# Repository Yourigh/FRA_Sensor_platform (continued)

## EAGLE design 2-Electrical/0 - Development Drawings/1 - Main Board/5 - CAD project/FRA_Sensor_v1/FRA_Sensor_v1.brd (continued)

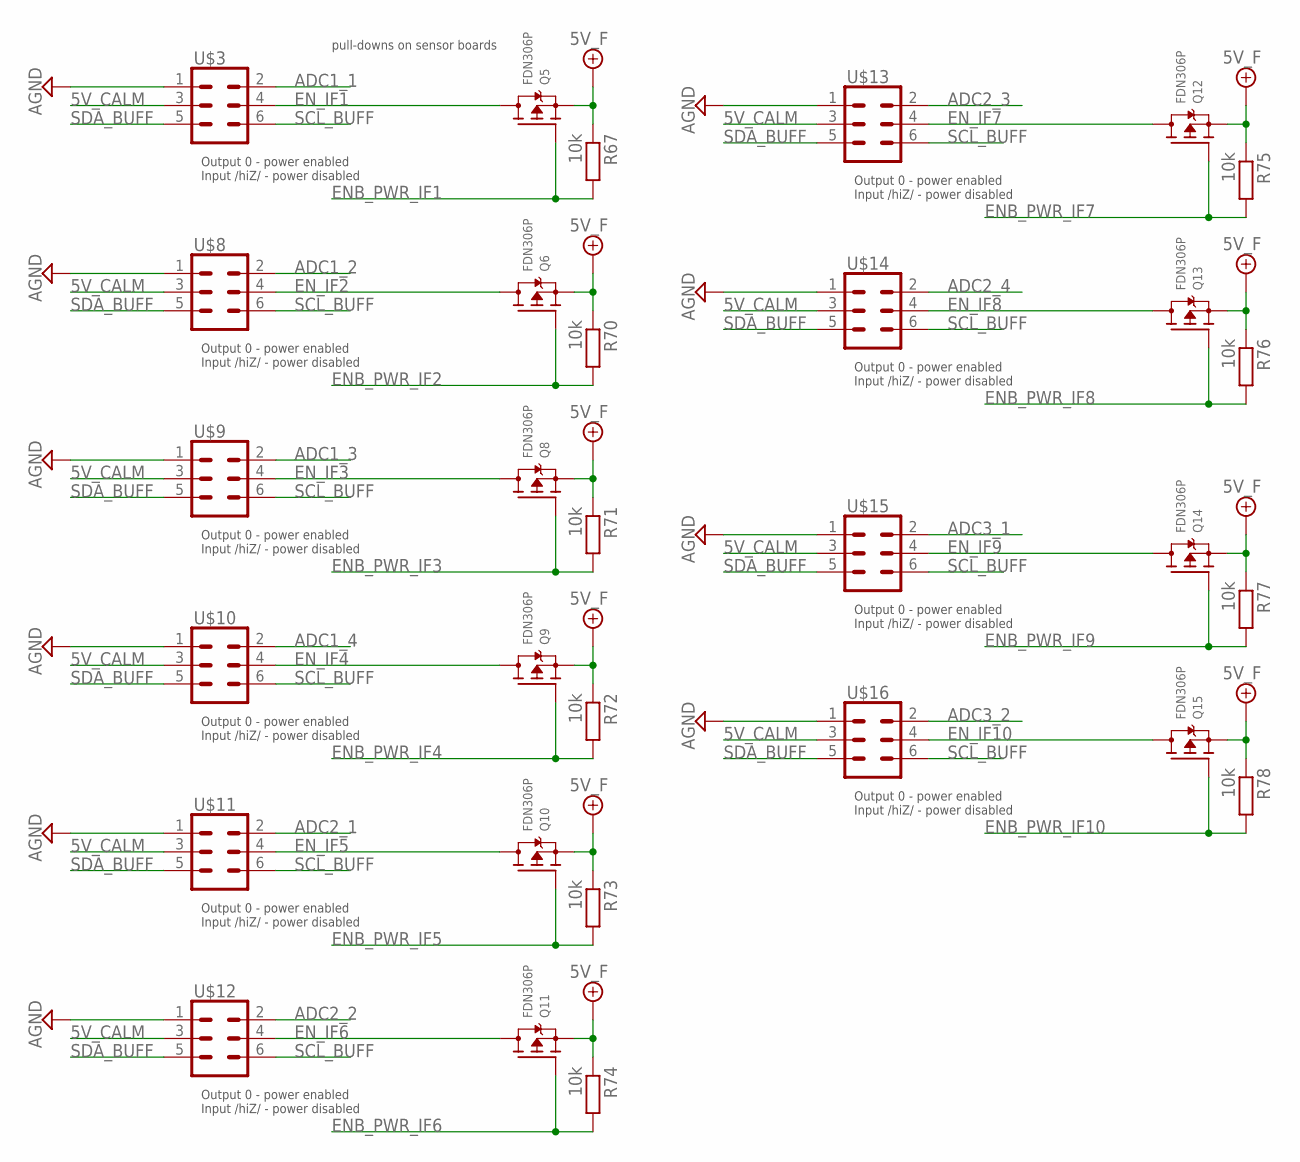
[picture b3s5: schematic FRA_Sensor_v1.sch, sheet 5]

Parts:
Q5, Q6, Q8, Q9, Q10, Q11, Q12, Q13, Q14, Q15: FDN306P; SOT23-WIDE; PARTNO FDN306P
R67, R70, R71, R72, R73, R74, R75, R76, R77, R78: 10k; R0603; PARTNO CRCW060310K0JNEAC
U$3, U$8, U$9, U$10, U$11, U$12, U$13, U$14, U$15, U$16: CONN_03X2_WE_61200621621; WE_61200621621; PARTNO 61200621621

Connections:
5V_CALM: U$3.3, U$8.3, U$9.3, U$10.3, U$11.3, U$12.3, U$13.3, U$14.3, U$15.3, U$16.3; also elsewhere on the board
+5V/1: Q5.2 (S), Q6.2 (S), Q8.2 (S), Q9.2 (S), Q10.2 (S), Q11.2 (S), Q12.2 (S), Q13.2 (S), Q14.2 (S), Q15.2 (S), R67.1, R70.1, R71.1, R72.1, R73.1, R74.1, R75.1, R76.1, R77.1, R78.1; also elsewhere on the board
ADC1_1: U$3.2; also elsewhere on the board
ADC1_2: U$8.2; also elsewhere on the board
ADC1_3: U$9.2; also elsewhere on the board
ADC1_4: U$10.2; also elsewhere on the board
ADC2_1: U$11.2; also elsewhere on the board
ADC2_2: U$12.2; also elsewhere on the board
ADC2_3: U$13.2; also elsewhere on the board
ADC2_4: U$14.2; also elsewhere on the board
ADC3_1: U$15.2; also elsewhere on the board
ADC3_2: U$16.2; also elsewhere on the board
AGND: U$3.1, U$8.1, U$9.1, U$10.1, U$11.1, U$12.1, U$13.1, U$14.1, U$15.1, U$16.1; also elsewhere on the board
ENB_PWR_IF1: Q5.1 (G), R67.2; also elsewhere on the board
ENB_PWR_IF2: Q6.1 (G), R70.2; also elsewhere on the board
ENB_PWR_IF3: Q8.1 (G), R71.2; also elsewhere on the board
ENB_PWR_IF4: Q9.1 (G), R72.2; also elsewhere on the board
ENB_PWR_IF5: Q10.1 (G), R73.2; also elsewhere on the board
ENB_PWR_IF6: Q11.1 (G), R74.2; also elsewhere on the board
ENB_PWR_IF7: Q12.1 (G), R75.2; also elsewhere on the board
ENB_PWR_IF8: Q13.1 (G), R76.2; also elsewhere on the board
ENB_PWR_IF9: Q14.1 (G), R77.2; also elsewhere on the board
ENB_PWR_IF10: Q15.1 (G), R78.2; also elsewhere on the board
EN_IF1: Q5.3 (D), U$3.4
EN_IF2: Q6.3 (D), U$8.4
EN_IF3: Q8.3 (D), U$9.4
EN_IF4: Q9.3 (D), U$10.4
EN_IF5: Q10.3 (D), U$11.4
EN_IF6: Q11.3 (D), U$12.4
EN_IF7: Q12.3 (D), U$13.4
EN_IF8: Q13.3 (D), U$14.4
EN_IF9: Q14.3 (D), U$15.4
EN_IF10: Q15.3 (D), U$16.4
SCL_BUFF: U$3.6, U$8.6, U$9.6, U$10.6, U$11.6, U$12.6, U$13.6, U$14.6, U$15.6, U$16.6; also elsewhere on the board
SDA_BUFF: U$3.5, U$8.5, U$9.5, U$10.5, U$11.5, U$12.5, U$13.5, U$14.5, U$15.5, U$16.5; also elsewhere on the board

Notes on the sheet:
Output 0 - power enabled Input /hiZ/ - power disabled
pull-downs on sensor boards

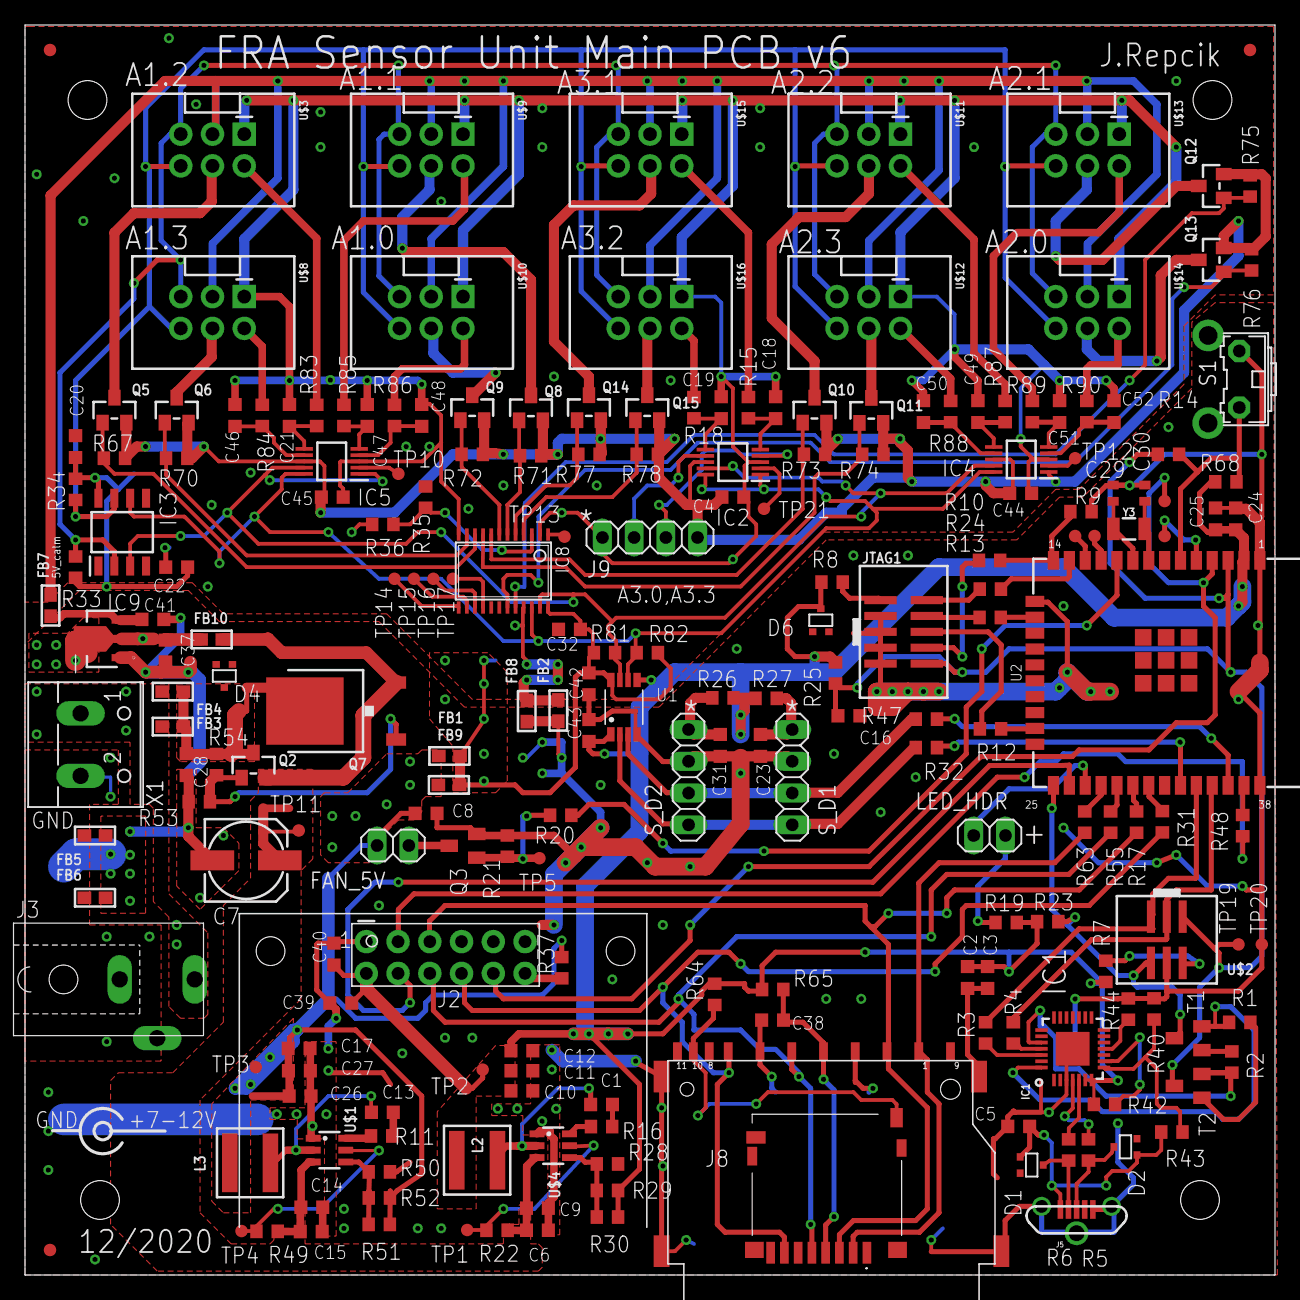
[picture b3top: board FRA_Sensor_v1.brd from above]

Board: 2 copper layers, 100.0 x 100.0 mm, 214 parts (1 on the bottom side), 138 nets.

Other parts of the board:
DRILEGEND: DRILEGEND

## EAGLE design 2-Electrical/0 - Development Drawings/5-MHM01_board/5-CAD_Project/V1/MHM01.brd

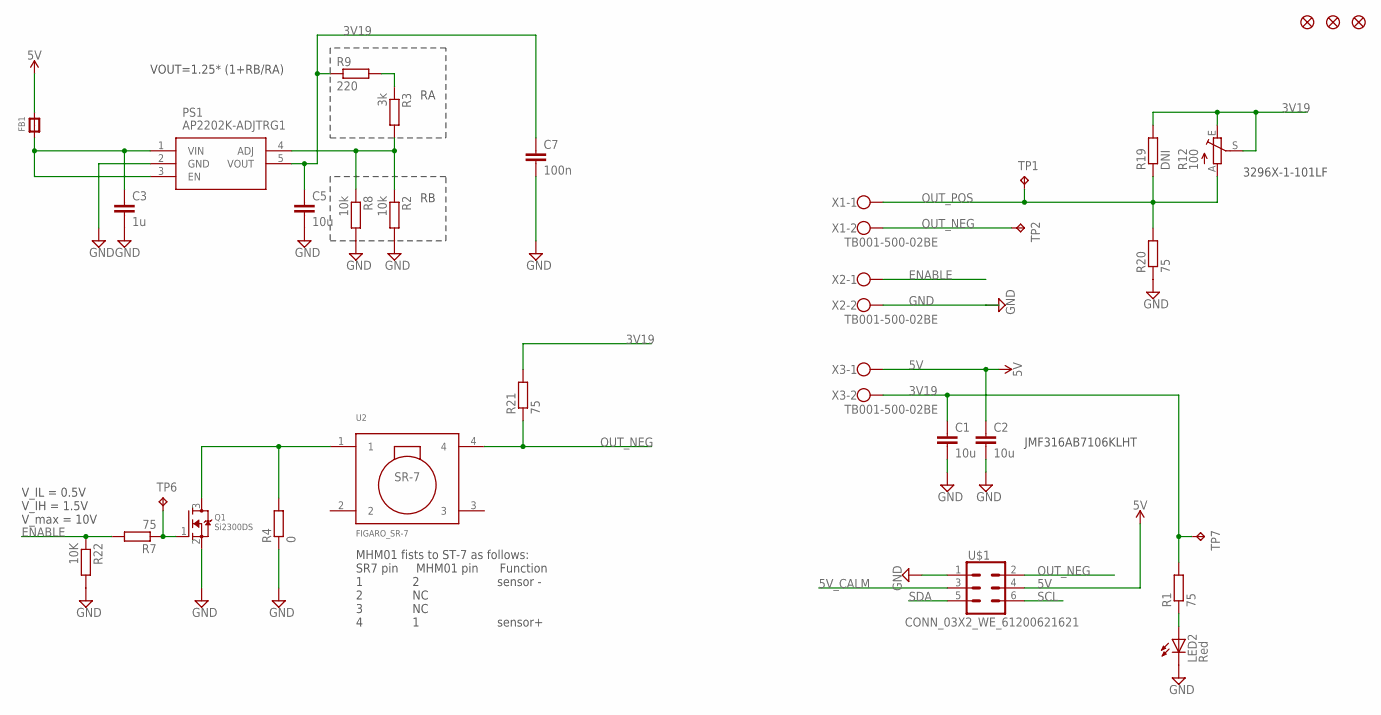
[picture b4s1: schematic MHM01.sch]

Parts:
C1, C2: 10u; C1206; PARTNO JMF316AB7106KLHT
C3: 1u; C0603K; PARTNO GRM188R71C105KE15D
C5: 10u; C0603K; PARTNO GRM188R61A106KE69J
C7: 100n; C0603K; PARTNO CC0603KRX7R8BB104
FB1: FERRITE; 0603; PARTNO BLM18PG121SN1D
FID1, FID2, FID4: FIDUCIAL""; FIDUCIAL_1MM
LED2: Red; CHIPLED_1206; PARTNO BR1101W-TR
PS1: AP2202K-ADJTRG1; SOT95P280X145-5N; PARTNO AP2202K-ADJTRG1
Q1: Si2300DS; SOT23; PARTNO JMF316AB7106KLHT
R1, R7, R20, R21: 75; R1206; PARTNO CRCW120675R0FKEA
R2, R8: 10k; R0603; PARTNO CRCW060310K0FKEA
R3: 3k; R0603; PARTNO ERA-3AEB302V
R4: 0; R1206; PARTNO CRCW12060000Z0EA
R9: 220; R0603; PARTNO CRCW0603220RFKEA
R12: 100; RJ9W; PARTNO 3296X-1-101LF
R19: DNI; R1206
R22: 10K; R1206; PARTNO CRCW120610K0FKEA
TP1, TP2, TP6, TP7: TPTP10R; TP10R
U2: FIGARO_SR-7; FIGARO-SR7; PARTNO SR-7
U$1: CONN_03X2_WE_61200621621; WE_61200621621; PARTNO 61200621621
X1, X2, X3: TB001-500-02BE; W237-102; PARTNO TB001-500-02BE

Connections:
3V19: C1.1, C5.1, C7.1, PS1.5 (VOUT), R1.2, R9.1, R12.E, R12.S, R19.2, R21.2, TP7.TP, X3.2
5V: C2.1, FB1.2, U$1.4, X3.1
5V_CALM: U$1.3
ENABLE: R7.2, R22.1, X2.1
GND: C1.2, C2.2, C3.2, C5.2, C7.2, LED2.C, PS1.2 (GND), Q1.2 (S), R2.2, R4.1, R8.2, R20.1, R22.2, U$1.1, X2.2
unnamed: LED2.A, R1.1
unnamed: PS1.4 (ADJ), R2.1, R3.2, R8.1
unnamed: C3.1, FB1.1, PS1.1 (VIN), PS1.3 (EN)
unnamed: Q1.3 (D), R4.2, U2.1
unnamed: R3.1, R9.2
unnamed: Q1.1 (G), R7.1, TP6.TP
OUT_NEG: R21.1, TP2.TP, U2.4, U$1.2, X1.2
OUT_POS: R12.A, R19.1, R20.2, TP1.TP, X1.1
SCL: U$1.6
SDA: U$1.5

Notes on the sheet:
MHM01 fists to ST-7 as follows: SR7 pin MHM01 pin Function 1 2 sensor - 2 NC 3 NC 4 1 sensor+
VOUT=1.25* (1+RB/RA)
JMF316AB7106KLHT
3296X-1-101LF
V_IL = 0.5V V_IH = 1.5V V_max = 10V

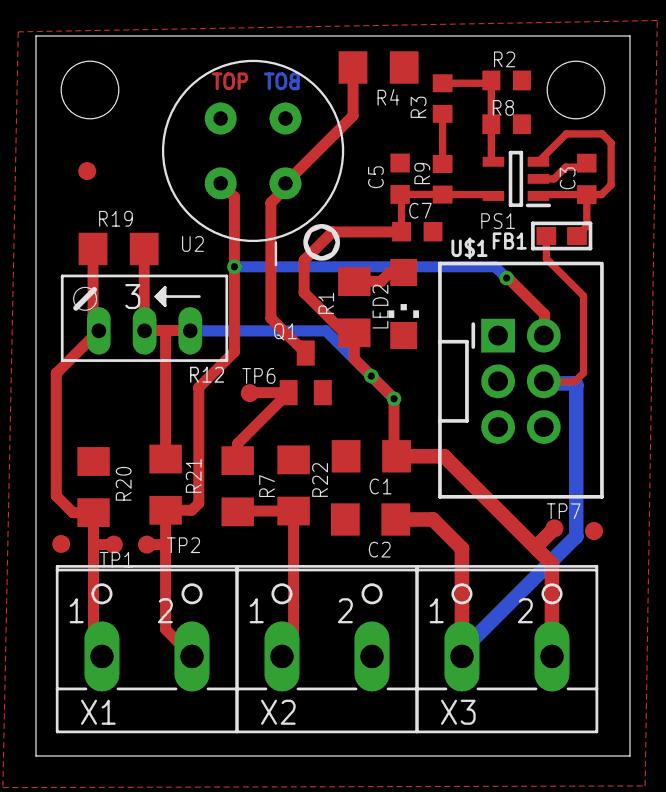
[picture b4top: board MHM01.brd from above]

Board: 2 copper layers, 33.0 x 40.0 mm, 33 parts (0 on the bottom side), 12 nets.

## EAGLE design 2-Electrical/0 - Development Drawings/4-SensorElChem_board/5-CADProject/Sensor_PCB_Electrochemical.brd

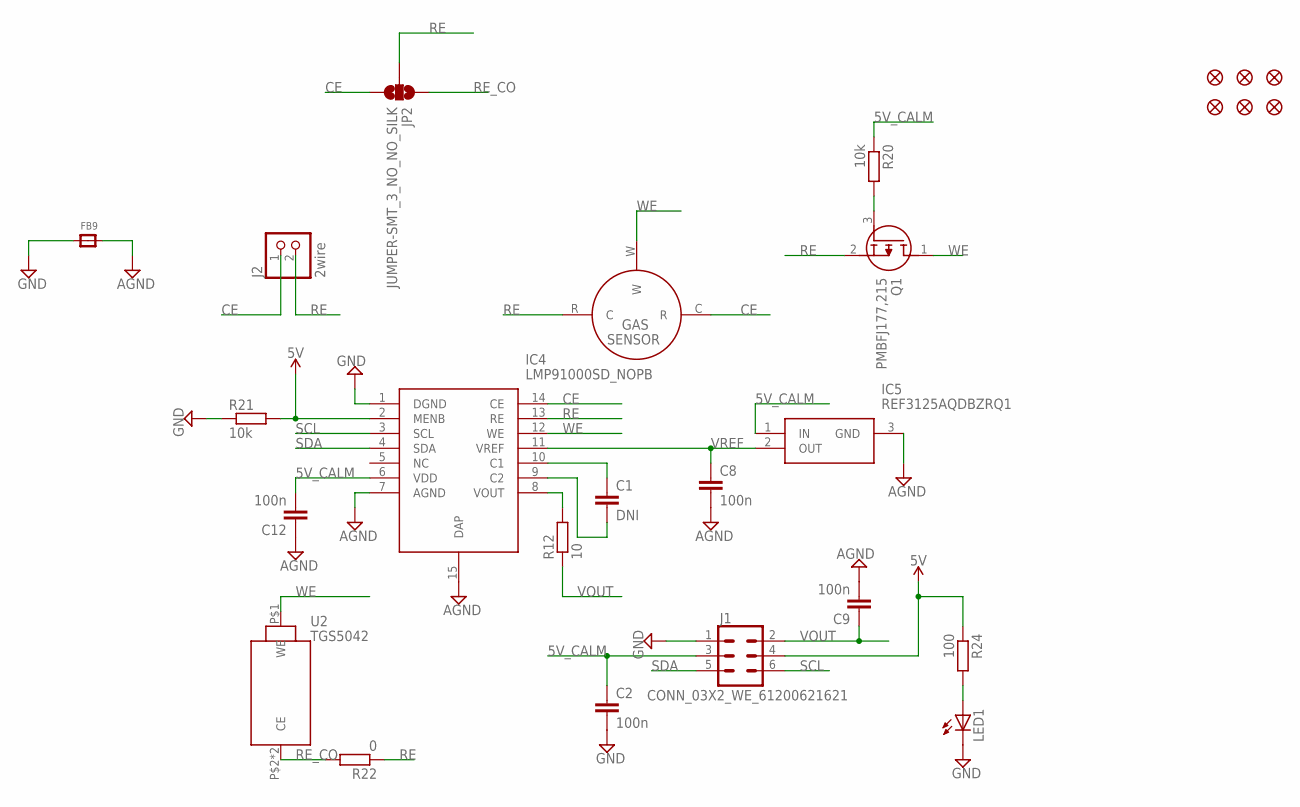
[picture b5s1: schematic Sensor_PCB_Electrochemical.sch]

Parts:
C1: DNI; C0603K
C2, C8, C9, C12: 100n; C0603K; PARTNO GRM188R71C104KA01D
FB9: FERRITE; 0603; PARTNO BLM18PG121SN1D
FID3, FID5, FID6, FID7, FID8, FID9: FIDUCIAL1X1UNMASKED; FIDUCIAL_1MM_UNMASKED
IC4: LMP91000SD_NOPB; SON50P400X400X80-15N; PARTNO LMP91000
IC5: REF3125AQDBZRQ1; SOT95P237X112-3N; PARTNO REF3125AQDBZRQ1
J1: CONN_03X2_WE_61200621621; WE_61200621621; PARTNO 30306-6002HB
J2: 2wire; 1X02; PARTNO TSW-102-07-G-S
JP2: JUMPER-SMT_3_NO_NO_SILK; SMT-JUMPER_3_0-NO_TRACE_NO-SILK
LED1: LEDCHIP-LED0603; CHIP-LED0603; PARTNO IN-S63AT5G
Q1: PMBFJ177,215; SOT95P230X110-3N; PARTNO PMBFJ177,215
R12: 10; R0603; PARTNO CRCW060310R0FKEA
R20, R21: 10k; R0603; PARTNO CRCW060310K0FKEA
R22: 0; R0603; PARTNO CRCW06030000Z0EA
R24: 100; R0603; PARTNO CRCW0603100RFKEA
U2: TGS5042; PARTNO INSTALLED_BY_CUSTOMER
X1: 3-ELECTRODE-GAS-SENSOR_SOCKET; 3-ELE_SOCKET_ANDON; PARTNO INSTALLED_BY_CUSTOMER

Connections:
5V: IC4.2 (MENB), J1.4, R21.2, R24.1
5V_CALM: C2.1, C12.2, IC4.6 (VDD), IC5.1 (IN), J1.3, R20.1
AGND: C8.2, C9.2, C12.1, FB9.2, IC4.7 (AGND), IC4.15 (DAP), IC5.3 (GND)
CE: IC4.14 (CE), J2.1, JP2.3, X1.C (R)
GND: C2.2, FB9.1, IC4.1 (DGND), J1.1, LED1.C, R21.1
unnamed: LED1.A, R24.2
unnamed: C1.1, IC4.10 (C1)
unnamed: IC4.8 (VOUT), R12.2
unnamed: C1.2, IC4.9 (C2)
unnamed: Q1.3 (G), R20.2
RE: IC4.13 (RE), J2.2, JP2.2, Q1.2 (S), R22.1, X1.R (C)
RE_CO: JP2.1, R22.2, U2.P$2 (CE), U2.P$3 (CE)
SCL: IC4.3 (SCL), J1.6
SDA: IC4.4 (SDA), J1.5
VOUT: C9.1, J1.2, R12.1
VREF: C8.1, IC4.11 (VREF), IC5.2 (OUT)
WE: IC4.12 (WE), Q1.1 (D), U2.P$1 (WE), X1.W

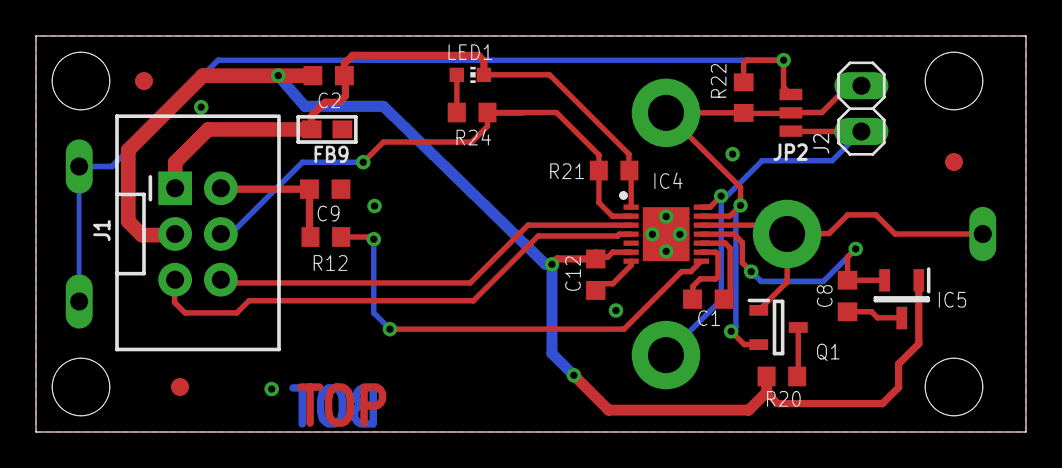
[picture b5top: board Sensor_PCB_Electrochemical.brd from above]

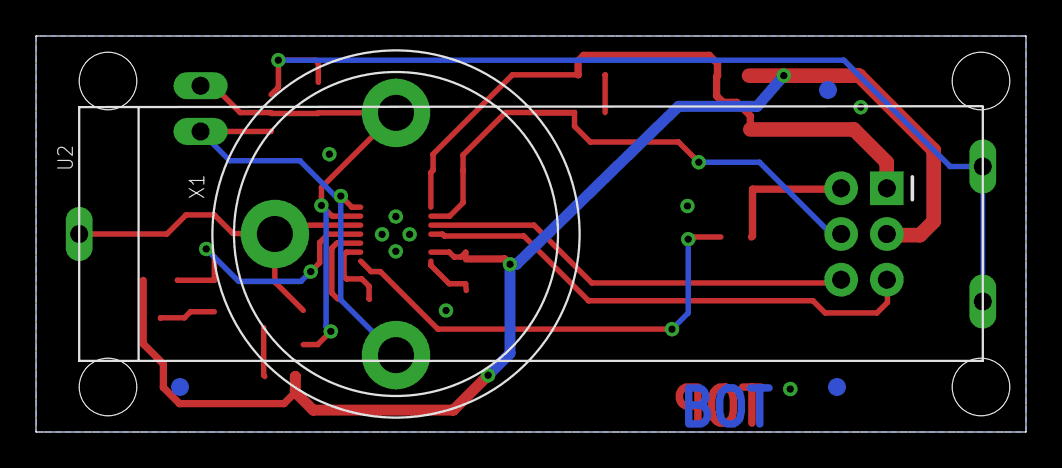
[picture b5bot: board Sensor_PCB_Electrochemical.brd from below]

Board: 2 copper layers, 55.0 x 22.0 mm, 27 parts (5 on the bottom side), 17 nets.

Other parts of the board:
DRILEGEND: DRILEGEND

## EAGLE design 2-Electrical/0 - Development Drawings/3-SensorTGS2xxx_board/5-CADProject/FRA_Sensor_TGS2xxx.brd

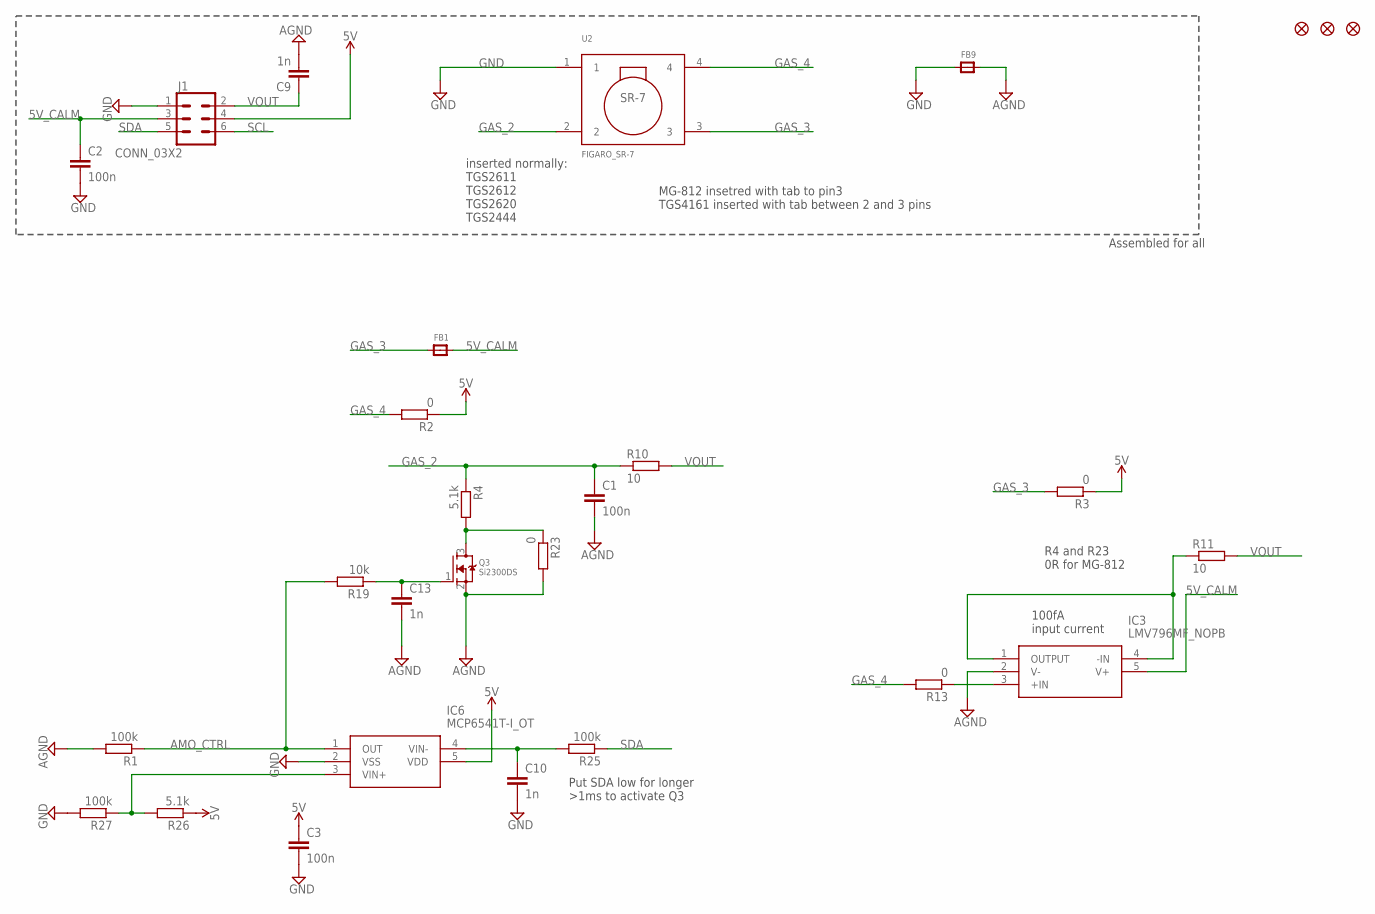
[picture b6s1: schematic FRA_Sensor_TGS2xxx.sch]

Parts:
C1, C2, C3: 100n; C0603K; PARTNO GRM188R71C104KA01D
C9, C10, C13: 1n; C0603K; PARTNO GRM188R71H102KA01D
FB1, FB9: FERRITE; 0603; PARTNO BLM18PG121SN1D
FID1, FID2, FID4: FIDUCIAL""; FIDUCIAL_1MM
IC3: LMV796MF_NOPB; SOT95P280X145-5N; PARTNO LMV796MF
IC6: MCP6541T-I_OT; SOT95P270X145-5N; PARTNO MCP6541T-I/OT
J1: CONN_03X2; WE_61200621621; PARTNO 30306-6002HB
Q3: Si2300DS; SOT23; PARTNO SI2300DS-T1-GE3
R1, R25, R27: 100k; R0603; PARTNO CRCW0603100KFKEA
R2, R3, R13, R23: 0; R0603; PARTNO CRCW06030000Z0EA
R4, R26: 5.1k; R0603; PARTNO CRCW06035K10FKEA
R10, R11: 10; R0603; PARTNO CRCW060310R0FKEA
R19: 10k; R0603; PARTNO CRCW060310K0FKEA
U2: FIGARO_SR-7; FIGARO-SR7; PARTNO installed_by_customer

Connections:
5V: C3.1, IC6.5 (VDD), J1.4, R2.1, R3.1, R26.1
5V_CALM: C2.1, FB1.2, IC3.5 (V+), J1.3
AGND: C1.2, C9.2, C13.2, FB9.2, IC3.2 (V-), Q3.2 (S), R1.2, R23.2
AMO_CTRL: IC6.1 (OUT), R1.1, R19.2
GAS_2: C1.1, R4.1, R10.1, U2.2
GAS_3: FB1.1, R3.2, U2.3
GAS_4: R2.2, R13.2, U2.4
GND: C2.2, C3.2, C10.2, FB9.1, IC6.2 (VSS), J1.1, R27.2, U2.1
unnamed: IC3.1 (OUTPUT), IC3.4 (-IN), R11.1
unnamed: C13.1, Q3.1 (G), R19.1
unnamed: IC3.3 (+IN), R13.1
unnamed: Q3.3 (D), R4.2, R23.1
unnamed: C10.1, IC6.4 (VIN-), R25.2
unnamed: IC6.3 (VIN+), R26.2, R27.1
SCL: J1.6
SDA: J1.5, R25.1
VOUT: C9.1, J1.2, R10.2, R11.2

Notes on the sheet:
100fA input current
inserted normally: TGS2611 TGS2612 TGS2620 TGS2444
Put SDA low for longer >1ms to activate Q3
MG-812 insetred with tab to pin3 TGS4161 inserted with tab between 2 and 3 pins
Assembled for all
R4 and R23 0R for MG-812

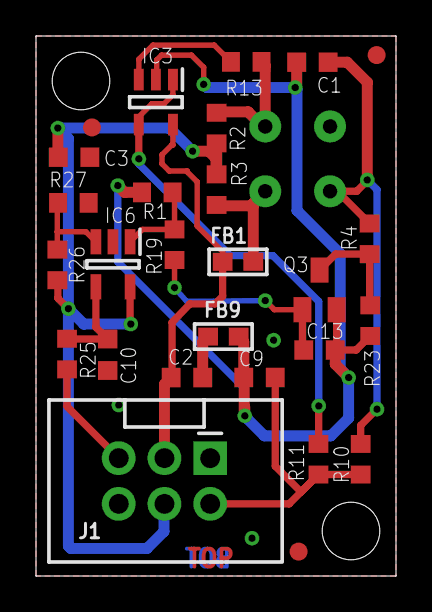
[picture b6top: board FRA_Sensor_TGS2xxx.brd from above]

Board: 2 copper layers, 20.0 x 30.0 mm, 29 parts (1 on the bottom side), 16 nets.

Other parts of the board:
DRILEGEND: DRILEGEND

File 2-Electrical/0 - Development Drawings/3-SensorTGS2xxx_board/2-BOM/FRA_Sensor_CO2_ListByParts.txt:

Part	Value	Attributes	Package	Description	Part Num
C1(DNP)	100n		C0603K	CAPACITOR, European symbol	GRM188R71C104KA01D
C2	100n		C0603K	CAPACITOR, European symbol	GRM188R71C104KA01D
C3	100n		C0603K	CAPACITOR, European symbol	GRM188R71C104KA01D
C9	100n		C0603K	CAPACITOR, European symbol	GRM188R71H102KA01D
C10(DNP)	1n		C0603K	CAPACITOR, European symbol	GRM188R71H102KA01D
C13(DNP)	100n		C0603K	CAPACITOR, European symbol	GRM188R71C104KA01D
FB1(DNP)			0603	Ferrite Bead	BLM18PG121SN1D
FB9			0603	Ferrite Bead	BLM18PG121SN1D
FID1	FIDUCIAL""		FIDUCIAL_1MM	Fiducial Alignment Points	*
FID2	FIDUCIAL""		FIDUCIAL_1MM	Fiducial Alignment Points	*
FID4	FIDUCIAL""		FIDUCIAL_1MM	Fiducial Alignment Points	*
IC3	LMV796MF_NOPB		SOT95P280X145-5N	Single 17 MHz, low noise, CMOS input, 1.8V operational amplifier	LMV796MF
IC6(DNP)	MCP6541T-I_OT		SOT95P270X145-5N	Comparator Push-Pull RRIO 1.6V SOT23-5	MCP6541T-I/OT
J1	CONN_03X2		WE_61200621621	https://eu.mouser.com/ProductDetail/Wurth-Elektronik/6120062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	30306-6002HB
Q3(DNP)	Si2300DS		SOT23	N-Channel Mosfet	SI2300DS-T1-GE3
R1(DNP)	100k		R0603	RESISTOR, European symbol	CRCW0603100KFKEA
R2(DNP)	0		R0603	RESISTOR, European symbol	CRCW06030000Z0EA
R3	0		R0603	RESISTOR, European symbol	CRCW06030000Z0EA
R4	0		R0603	RESISTOR, European symbol	CRCW06035K10FKEA
R10(DNP)	10		R0603	RESISTOR, European symbol	CRCW060310R0FKEA
R11	10		R0603	RESISTOR, European symbol	CRCW060310R0FKEA
R13	0		R0603	RESISTOR, European symbol	CRCW06030000Z0EA
R19	10k		R0603	RESISTOR, European symbol	CRCW060310K0FKEA
R23	0		R0603	RESISTOR, European symbol	CRCW06030000Z0EA
R25(DNP)	100k		R0603	RESISTOR, European symbol	CRCW0603100KFKEA
R26(DNP)	5.1k		R0603	RESISTOR, European symbol	CRCW06035K10FKEA
R27(DNP)	100k		R0603	RESISTOR, European symbol	CRCW0603100KFKEA
U2	FIGARO_SR-7		FIGARO-SR7		INSTALLED_BY_CUSTOMER

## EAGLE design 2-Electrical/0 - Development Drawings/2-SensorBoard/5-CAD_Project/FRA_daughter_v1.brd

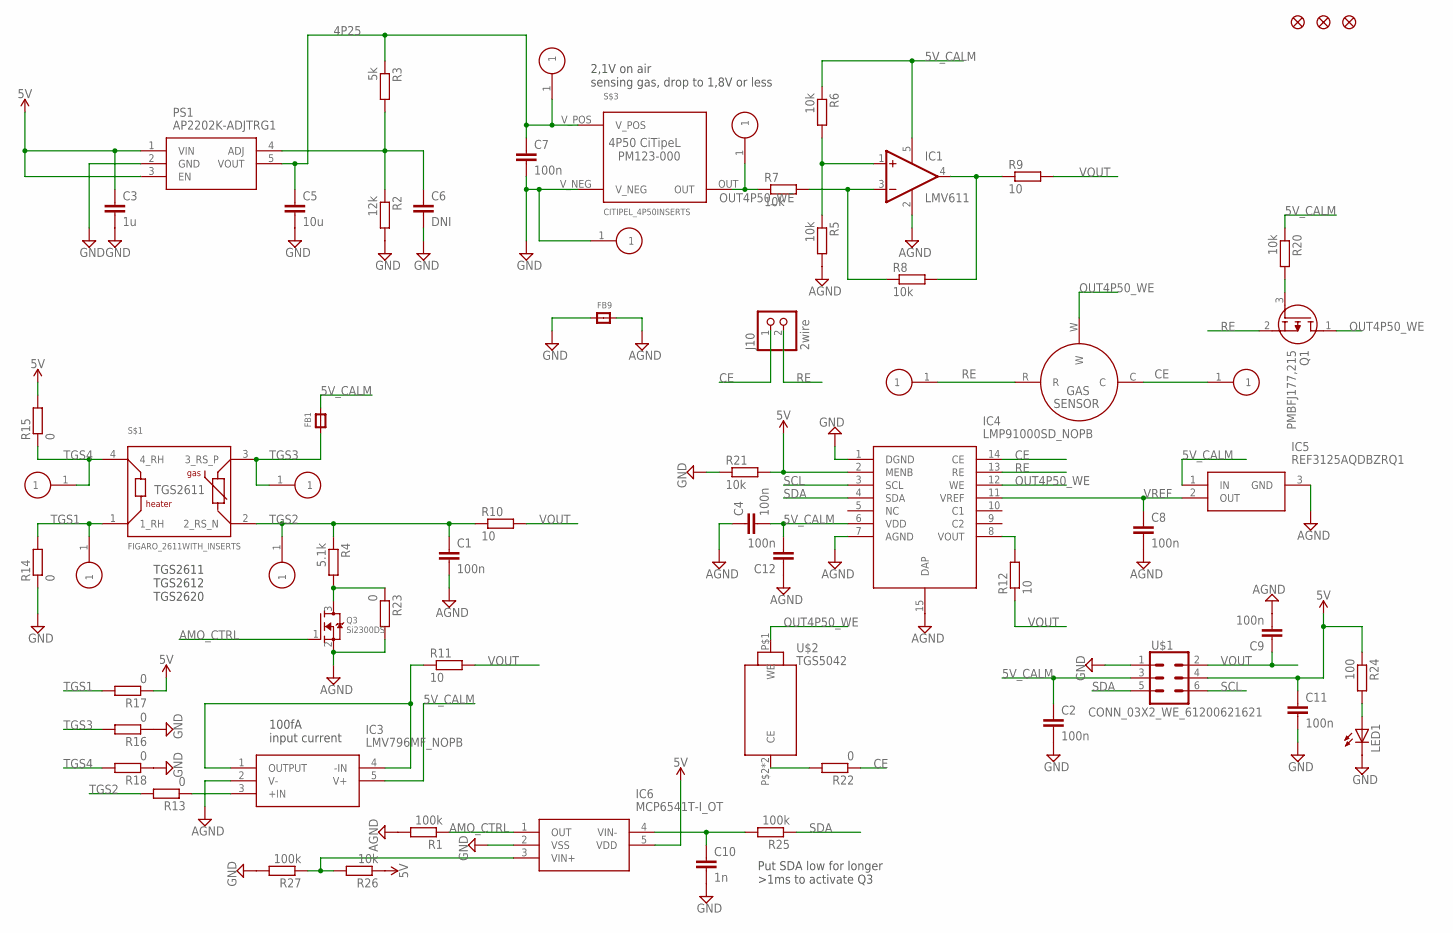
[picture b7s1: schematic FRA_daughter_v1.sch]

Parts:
C1, C2, C4, C7, C8, C9, C11, C12: 100n; C0603K
C3: 1u; C0603K
C5: 10u; C0603K
C6: DNI; C0603K
C10: 1n; C0603K
FB1, FB9: FERRITE; 0603; PARTNO BLM18PG121SN1D
FID1, FID2, FID4: FIDUCIAL""; FIDUCIAL_1MM
IC1: LMV611; SC70-5L
IC3: LMV796MF_NOPB; SOT95P280X145-5N
IC4: LMP91000SD_NOPB; SON50P400X400X80-15N
IC5: REF3125AQDBZRQ1; SOT95P237X112-3N
IC6: MCP6541T-I_OT; SOT95P270X145-5N
J1, J6, J7, J8, J9: INSERT_MM5_06691.5MM; INSERT_1MM5_9372
J2: TGS3; INSERT_MM5_0669
J3: TGS2; INSERT_MM5_0669
J4: TGS1; INSERT_MM5_0669
J5: TGS4; INSERT_MM5_0669
J10: 2wire; 1X02; PARTNO TSW-102-07-G-S
LED1: LEDCHIP-LED0603; CHIP-LED0603
PS1: AP2202K-ADJTRG1; SOT95P280X145-5N
Q1: PMBFJ177,215; SOT95P230X110-3N
Q3: Si2300DS; SOT23
R1, R25, R27: 100k; R0603
R2: 12k; R0603
R3: 5k; R0603
R4: 5.1k; R0603
R5, R6, R7, R8, R20, R21, R26: 10k; R0603
R9, R10, R11, R12: 10; R0603
R13, R14, R15, R16, R17, R18, R22, R23: 0; R0603
R24: 100; R0603
S$1: FIGARO_2611WITH_INSERTS; TH4_TGS2611_INSERTS
S$3: CITIPEL_4P50INSERTS; TH3_4P50_INSERTS
U$1: CONN_03X2_WE_61200621621; WE_61200621621
U$2: TGS5042
X1: 3-ELECTRODE-GAS-SENSORINS; 3-ELECTRODE_INSETRS

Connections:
4P25: C5.1, C7.1, J6.1, PS1.5 (VOUT), R3.1, S$3.V_POS
5V: C3.1, C11.1, IC4.2 (MENB), IC6.5 (VDD), PS1.1 (VIN), PS1.3 (EN), R15.2, R17.1, R21.2, R24.1, R26.1, U$1.4
5V_CALM: C2.1, C4.2, C12.2, FB1.2, IC1.5 (V+), IC3.5 (V+), IC4.6 (VDD), IC5.1 (IN), R6.1, R20.1, U$1.3
AGND: C1.2, C4.1, C8.2, C9.2, C12.1, FB9.2, IC1.2 (V-), IC3.2 (V-), IC4.7 (AGND), IC4.15 (DAP), IC5.3 (GND), Q3.2 (S), R1.2, R5.2, R23.2
AMO_CTRL: IC6.1 (OUT), Q3.1 (G), R1.1
CE: IC4.14 (CE), J9.1, J10.1, R22.1, X1.C
GND: C2.2, C3.2, C5.2, C6.2, C7.2, C10.2, C11.2, FB9.1, IC4.1 (DGND), IC6.2 (VSS), J1.1, LED1.C, PS1.2 (GND), R2.2, R14.1, R16.1, R18.1, R21.1, R27.2, S$3.V_NEG, U$1.1
unnamed: LED1.A, R24.2
unnamed: C6.1, PS1.4 (ADJ), R2.1, R3.2
unnamed: IC4.8 (VOUT), R12.2
unnamed: IC1.1 (+IN), R5.1, R6.2
unnamed: IC1.3 (-IN), R7.2, R8.1
unnamed: IC1.4 (OUT), R8.2, R9.1
unnamed: IC3.1 (OUTPUT), IC3.4 (-IN), R11.1
unnamed: Q1.3 (G), R20.2
unnamed: IC3.3 (+IN), R13.1
unnamed: Q3.3 (D), R4.2, R23.1
unnamed: R22.2, U$2.P$2 (CE), U$2.P$3 (CE)
unnamed: C10.1, IC6.4 (VIN-), R25.2
unnamed: IC6.3 (VIN+), R26.2, R27.1
OUT4P50_WE: IC4.12 (WE), J7.1, Q1.1 (D), R7.1, S$3.OUT, U$2.P$1 (WE), X1.W
RE: IC4.13 (RE), J8.1, J10.2, Q1.2 (S), X1.R
SCL: IC4.3 (SCL), U$1.6
SDA: IC4.4 (SDA), R25.1, U$1.5
TGS1: J4.1, R14.2, R17.2, S$1.1 (1_RH)
TGS2: C1.1, J3.1, R4.1, R10.1, R13.2, S$1.2 (2_RS_N)
TGS3: FB1.1, J2.1, R16.2, S$1.3 (3_RS_P)
TGS4: J5.1, R15.1, R18.2, S$1.4 (4_RH)
VOUT: C9.1, R9.2, R10.2, R11.2, R12.1, U$1.2
VREF: C8.1, IC4.11 (VREF), IC5.2 (OUT)

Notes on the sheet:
100fA input current
2,1V on air sensing gas, drop to 1,8V or less
TGS2611 TGS2612 TGS2620
Put SDA low for longer >1ms to activate Q3

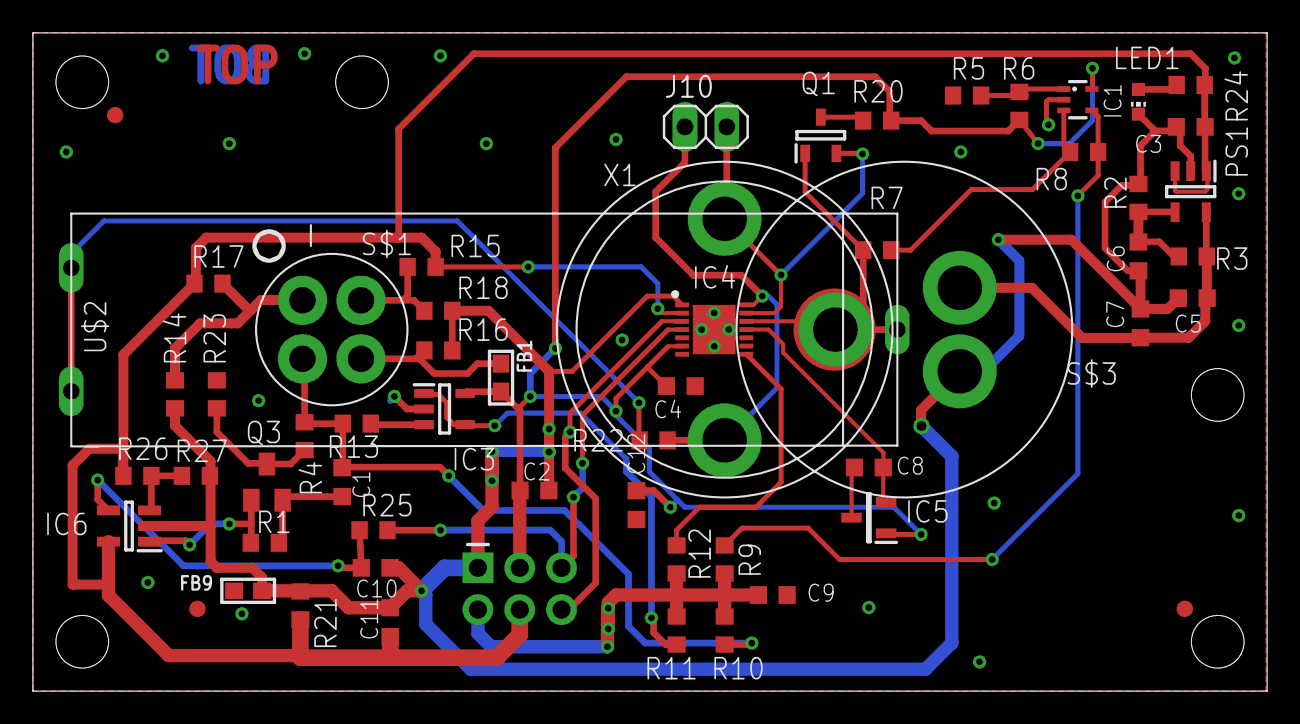
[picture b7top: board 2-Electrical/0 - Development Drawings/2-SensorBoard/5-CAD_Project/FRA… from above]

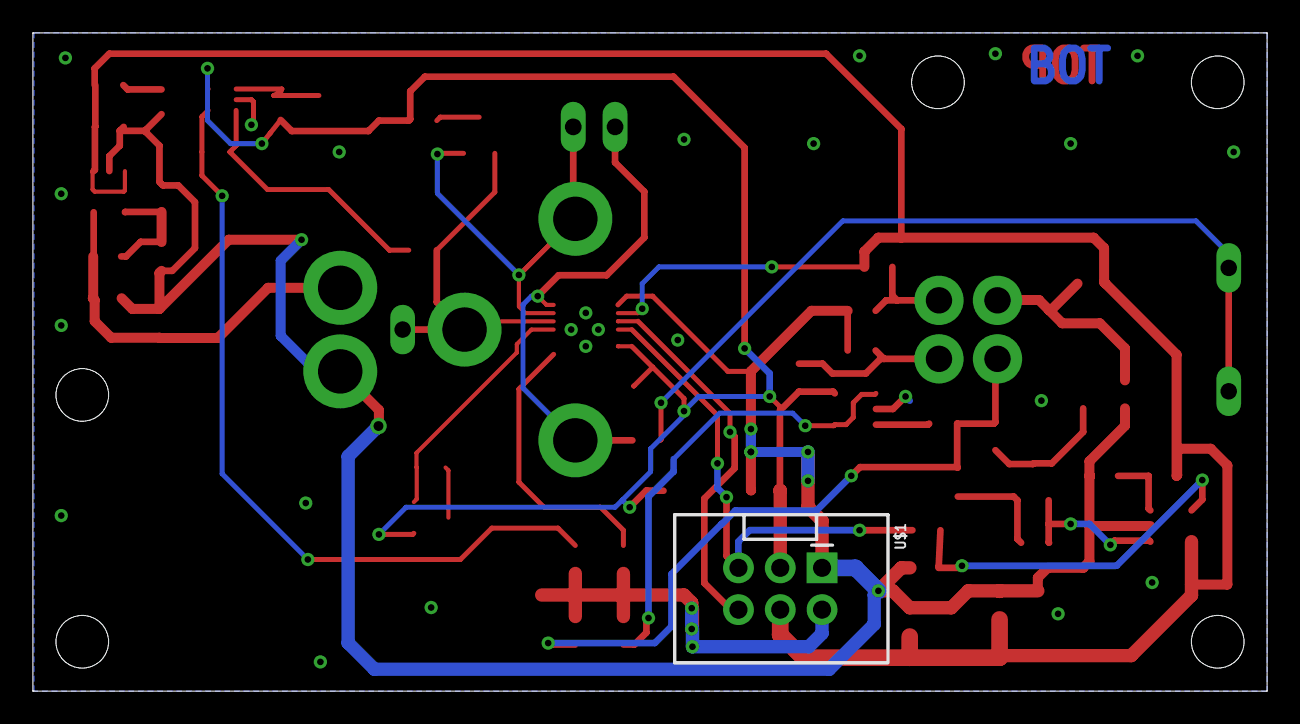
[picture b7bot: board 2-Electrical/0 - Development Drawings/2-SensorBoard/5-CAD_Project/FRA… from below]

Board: 2 copper layers, 75.0 x 40.0 mm, 67 parts (7 on the bottom side), 30 nets.

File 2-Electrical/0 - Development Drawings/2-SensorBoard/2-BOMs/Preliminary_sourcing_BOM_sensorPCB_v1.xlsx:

Part |  | Value | Device | Package | Note
C1 |  | 1n | C-EUC0603K | C0603K
C2 |  | 100n | C-EUC0603K | C0603K
C3 |  | 1u | C-EUC0603K | C0603K
C5 |  | 10u | C-EUC0603K | C0603K
C7 |  | 100n | C-EUC0603K | C0603K
C8 |  | 100n | C-EUC0603K | C0603K
C9 |  | 100n | C-EUC0603K | C0603K
C10 |  | 1n | C-EUC0603K | C0603K
C11 |  | 100n | C-EUC0603K | C0603K
C12 |  | 100n | C-EUC0603K | C0603K
C13 |  | 100n | C-EUC0603K | C0603K
FB1 |  |  | FERRITE | 603 | same as on main and recent order
FB9 |  |  | FERRITE | 603 | same as on main and recent order
IC1 |  | LMV611 | OPA333DCK | SC70-5L |  | for 4p50 sensor
IC3 |  | LMV796MF_NOPB | LMV796MF_NOPB | SOT95P280X145-5N |  | for CO2
IC4 |  | LMP91000SD_NOPB | LMP91000SD_NOPB | SON50P400X400X80-15N |  | for elchem
IC5 |  | REF3125AQDBZRQ1 | REF3125AQDBZRQ1 | SOT95P237X112-3N | not assembled | for elchem
IC6 |  | MCP6541T-I_OT | MCP6541T-I_OT | SOT95P270X145-5N |  | for amonia
J1 |  | INSERT_MM5_06691.5MM | INSERT_MM5_06691.5MM | INSERT_1MM5_9372
J10 |  | 2wire | PINHD-1X2 | 1X02 | same as on main - pin 2.54mm header for jumper
LED1 |  |  | LEDCHIP-LED0603 | CHIP-LED0603 | find some 0603 LED in package, or remove
PS1 |  | AP2202K-ADJTRG1 | AP2202K-ADJTRG1 | SOT95P280X145-5N |  | for 4p50 sensor
Q1 |  | PMBFJ177,215 | PMBFJ177,215 | SOT95P230X110-3N |  | for elchem
Q3 |  | Si2300DS | MOSFET-NREFLOW | SOT23 |  | for amonia
R1 |  | 100k | R-EU_R0603 | R0603
R2 |  | 12k | R-EU_R0603 | R0603 |  | for 4p50 sensor
R3 |  | 5k | R-EU_R0603 | R0603 |  | for 4p50 sensor
R4 |  | 5.1k | R-EU_R0603 | R0603
R5 |  | 10k | R-EU_R0603 | R0603
R6 |  | 10k | R-EU_R0603 | R0603
R7 |  | 10k | R-EU_R0603 | R0603
R8 |  | 10k | R-EU_R0603 | R0603
R9 |  | 10 | R-EU_R0603 | R0603
R10 |  | 10 | R-EU_R0603 | R0603
R11 |  | 10 | R-EU_R0603 | R0603
R12 |  | 10 | R-EU_R0603 | R0603
R13 |  | 0 | R-EU_R0603 | R0603
R14 |  | 0 | R-EU_R0603 | R0603
R15 |  | 0 | R-EU_R0603 | R0603
R16 |  | 0 | R-EU_R0603 | R0603
R17 |  | 0 | R-EU_R0603 | R0603
R18 |  | 0 | R-EU_R0603 | R0603
R19 |  | 10k | R-EU_R0603 | R0603 | in past order
R20 |  | 10k | R-EU_R0603 | R0603
R21 |  | 10k | R-EU_R0603 | R0603
R22 |  | 0 | R-EU_R0603 | R0603 | in past order
R23 |  | 0 | R-EU_R0603 | R0603
R24 |  | 100 | R-EU_R0603 | R0603
R25 |  | 100k | R-EU_R0603 | R0603 | in recent order
R26 |  | 5.1k | R-EU_R0603 | R0603 | in recent order
R27 |  | 100k | R-EU_R0603 | R0603 | in recent order
U$1 |  | CONN_03X2_WE_61200621621 | CONN_03X2_WE_61200621621 | WE_61200621621 |  | for all
 |  | connector for elchem
 |  | connector for TGS

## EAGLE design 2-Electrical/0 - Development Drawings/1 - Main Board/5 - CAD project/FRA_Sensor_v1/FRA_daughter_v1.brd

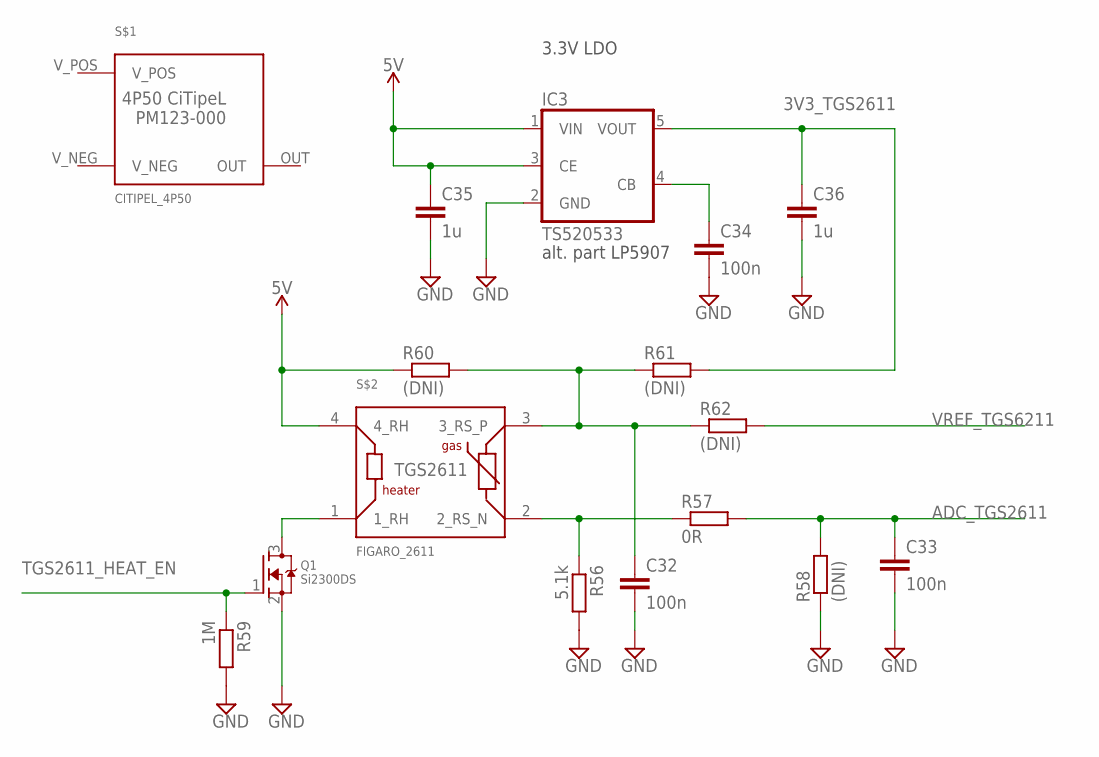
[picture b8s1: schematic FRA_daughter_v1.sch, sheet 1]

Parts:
C32, C33, C34: 100n; C0603K
C35, C36: 1u; C0603K
IC3: TS520533; SOT25
Q1: Si2300DS; SOT23
R56: 5.1k; R0603
R57: 0R; R0603
R58, R60, R61, R62: (DNI); R0603
R59: 1M; R0603
S$1: CITIPEL_4P50; TH3_4P50
S$2: FIGARO_2611; TH4_TGS2611

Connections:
3V3_TGS2611: C36.1, IC3.5 (VOUT), R61.2
5V: C35.1, IC3.1 (VIN), IC3.3 (CE), R60.1, S$2.4 (4_RH)
ADC_TGS2611: C33.1, R57.2, R58.2
GND: C32.2, C33.2, C34.2, C35.2, C36.2, IC3.2 (GND), Q1.2 (S), R56.2, R58.1, R59.2; also elsewhere on the board
unnamed: Q1.3 (D), S$2.1 (1_RH)
unnamed: C34.1, IC3.4 (CB)
RS_NEG: R56.1, R57.1, S$2.2 (2_RS_N)
RS_POS: C32.1, R60.2, R61.1, R62.1, S$2.3 (3_RS_P)
TGS2611_HEAT_EN: Q1.1 (G), R59.1
VREF_TGS6211: R62.2
V_NEG: S$1.V_NEG
V_POS: S$1.V_POS

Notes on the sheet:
alt. part LP5907
3.3V LDO

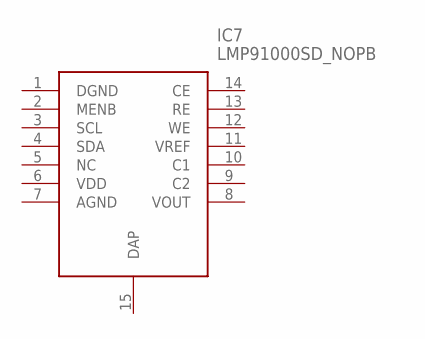
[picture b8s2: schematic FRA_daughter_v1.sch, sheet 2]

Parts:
IC7: LMP91000SD_NOPB; SON50P400X400X80-15N

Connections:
AGND: IC7.7 (AGND)
DAP: IC7.15 (DAP)
DGND: IC7.1 (DGND)
VDD: IC7.6 (VDD)
